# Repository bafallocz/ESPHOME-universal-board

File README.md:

# ESPHOME-universal-board

Modular, multi-purpose automation control boards designed around the **Seeed Studio XIAO** form-factor (ESP32-C3 / S3 / RP2040), tailored for **ESPHome**, **Home Assistant**, and standalone embedded automation projects.

The system consists of three hardware revisions/modules:
1. **Universal Board (Full Version)** – High-density I/O, mains-powered, precision analog/PWM expansion, gate-driven power MOSFETs, and relays.
2. **Universal Board (Light Version)** – Compact DC-powered board with direct logic-level SMD MOSFETs, relays, and inputs.
3. **Relay Expansion Board (Stackable)** – Dedicated 5-channel relay daughterboard controlled via the Full version's I2C PWM expander.

---

## Hardware Overview & Specifications

### 1. Board One: Full Version (Flagship)

Designed as a central automation node capable of direct 230 V mains operation, multi-channel high-current PWM control, mixed-signal ADC/DAC sensing, and galvanic isolation.

* **Core MCU:** Socket for Seeed Studio XIAO module (ESP32-C3, ESP32-S3, etc.).
* **Power Supply Options:**
  * **Mains AC Input:** Onboard **Hi-Link HLK-20M12** (20 W, 12 V / 1.66 A) isolated AC/DC power supply.
  * **Mains Protection:** 10D561K Metal Oxide Varistor (MOV) for surge and transient suppression.
  * **DC Input:** 2.1 mm DC Barrel Jack (`PJ-102AH`) for external 12 V DC supply.
  * **Step-Down:** Footprint for LM7805 LDO or pin-compatible high-efficiency DC-DC switching buck regulator (12 V to 5 V).
* **Power Outputs (4x High-Current PWM):**
  * **MOSFETs:** TO-220 footprint (tested with **IRL540N** / **IRFB4110PBF**).
  * **Gate Drivers:** Dual high-speed drivers (**TC4427** running at 12 V rail). Delivers up to 1.5 A peak gate drive current for fast switching transitions and minimal thermal loss during high-frequency PWM.
  * **Ratings:** Up to 60 V DC, 10 A burst / 5 A continuous per channel (dependent on PCB copper weight and heatsinking).
* **Analog & Precision I/O:**
  * **Analog Devices AD5593R** (12-bit, 8-channel configurable ADC / DAC / GPIO via I2C).
  * Onboard 2.5 V low-drift reference (`VREF`), filtered analog supplies, and dedicated 8-pin terminal/pin header.
* **Expanded PWM:**
  * **NXP PCA9685PW** (16-channel, 12-bit I2C PWM controller).
  * Channel `LED0` can be routed to high-current output/dimming, remaining channels (`EX_PWM1`–`EX_PWM15`) routed to stack header `JP1`.
* **Relays (2x Isolated):**
  * **Songle SRD-05VDC-SL-C** SPDT relays (rated 250 VAC / 10 A, 30 VDC / 10 A).
  * **Isolation & Drive:** Opto-isolated via **CPC1018N** 1-Form-A Solid State Relays (SSR) to isolate MCU logic from inductive switching spikes.
  * Flyback protection diodes on each coil.
* **Digital Inputs (2x Terminals):**
  * Dedicated screw terminals with 1k series current limiting.
  * **Nexperia PESD3V3L2BT** TVS/ESD diode array for surge/ESD protection on 3.3 V logic.
* **Expansion:** All unused XIAO GPIOs routed to standard 2.54 mm pin headers (`PHD1`, `PHD2`).

---

### 2. Board Two: Light Version

A low-profile, cost-optimized DC-powered board ideal for decentralized sub-nodes, LED strip dimming, and valve/motor switching.

* **Core MCU:** Seeed Studio XIAO module footprint.
* **Power Supply:**
  * DC Barrel Jack (`PJ-102AH`) feeding a dedicated pin-compatible DC-DC Step-Down module.
  * USB-C 5 V powering option with selectable `U_SEL` power routing jumper.
* **Power Outputs (3x SMD PWM):**
  * **MOSFETs:** **AO3400A** (N-channel, 30 V / 5.7 A).
  * Driven directly from MCU GPIOs.
  * Ideal for 12 V / 24 V LED strips (up to 3 A continuous per channel without forced cooling).
* **Relays (2x):**
  * 2x **SRD-05VDC-SL-C** driven via **CPC1018N** solid-state optical switches.
* **Digital Inputs (2x):**
  * Terminal block inputs with pull-ups/pull-downs for reed switches, dry contacts, or external buttons.
* **Expansion:** Unused pins broken out to side headers for I2C or SPI sensors.

---

### 3. Board Three: Expansion Board (Stackable)

An add-on hat designed to mount directly onto the **Full Version** via headers `PHD1`, `PHD2`, and `JP1`.

* **5x Additional Relays:** **SRD-05VDC-SL-C** (230 VAC / 10 A contact rating).
* **Control Bus:** Driven directly by the Full Board’s **PCA9685** PWM/GPIO expander (`EX_PWM1` through `EX_PWM5`).
* **Isolation:** Each relay coil is switched through an independent **CPC1018N** optical isolation relay.
* **Pass-through Routing:**
  * Leaves `EX_PWM6`–`EX_PWM15` available for additional servo or PWM peripherals.
  * Passes through AD5593R DAC/ADC lines and spare MCU GPIOs.

---

## Hardware Operating Limits & Safety Guidelines

> [!WARNING]
> **Mains Voltage Hazard:** The Full Version contains exposed 230 VAC tracks. Always install in an insulated DIN-rail or 3D-printed enclosure (**FR MATERIAL**). Maintain appropriate creepage and clearance distances between mains tracks and low-voltage logic.

* **Relay Contacts:** Rated for 10 A @ 250 VAC resistive load. For inductive loads (motors, pumps, contactors).
* **Full Board PWM Channels:** While the MOSFETs (IRFB4110 / IRL540N) have high silicon current ratings.
* **Light Board PWM Channels:** AO3400A is rated for 5.7 A peak; recommended continuous load per channel is **2.5 A to 3 A** without a copper heatsink pour.
* **Power Supply Headroom:** The HLK-20M12 provides up to 1.66 A at 12 V. When running multiple relays and external 12 V loads simultaneously, verify total DC power consumption remains under 20 W.

---

## AD5593R ESPHome Component

This repository includes a custom ESPHome component for the **Analog Devices AD5593R** (8-channel 12-bit configurable ADC / DAC / GPIO).

### How to Import into ESPHome

Add the `external_components` block to your YAML configuration:

#### Option A: Direct from GitHub
```yaml
external_components:
  - source: github://bafallocz/ESPHOME-universal-board
    components: [ ad5593r ]
```

#### Option B: Local Component (when compiling inside this repo)
```yaml
external_components:
  - source: components
    components: [ ad5593r ]
```

---

### AD5593R Configuration Guide

Any of the 8 pins (`0` to `7`) can be independently configured as an **ADC input**, **DAC output**, **Digital input (`binary_sensor`)**, or **Digital output (`switch`)**.

#### 1. Hub Definition
```yaml
ad5593r:
  - id: ad5593r_hub
    i2c_id: bus_a
    address: 0x10
    # reference_voltage: 2.5V  # Internal reference (default 2.5V)
    # gain_2x: true            # Default true -> Full range 0 to 5.0 V
```

#### 2. Analog Outputs (DAC) - Channels 0 to 7
Outputs range from `0.0` (0 V) to `1.0` (5.0 V):
```yaml
output:
  - platform: ad5593r
    ad5593r_id: ad5593r_hub
    channel: 0
    id: dac_out_0

  - platform: ad5593r
    ad5593r_id: ad5593r_hub
    channel: 1
    id: dac_out_1
```

Control DAC outputs using a Home Assistant template slider:
```yaml
number:
  - platform: template
    name: "DAC 0 Output"
    min_value: 0
    max_value: 1
    step: 0.01
    mode: slider
    set_action:
      - output.set_level:
          id: dac_out_0
          level: !lambda 'return x;'
```

#### 3. Analog Inputs (ADC) & Internal Temperature Sensor
Reports voltage values in **Volts (V)**:
```yaml
sensor:
  - platform: ad5593r
    ad5593r_id: ad5593r_hub
    channel: 2
    name: "AD5593R Analog Input 2"
    update_interval: 1s

  - platform: ad5593r
    ad5593r_id: ad5593r_hub
    channel: 3
    name: "AD5593R Analog Input 3"
    update_interval: 1s

  # Chip Internal Temperature Sensor (°C)
  - platform: ad5593r
    ad5593r_id: ad5593r_hub
    channel: temperature
    name: "AD5593R Internal Temperature"
    update_interval: 10s
```

#### 4. Digital Inputs (`binary_sensor`)
Reads logic state from pins (with optional 85 kΩ internal pull-down):
```yaml
binary_sensor:
  - platform: ad5593r
    ad5593r_id: ad5593r_hub
    channel: 4
    name: "AD5593R Digital Input 4"
    pulldown: true
```

#### 5. Digital Outputs (`switch`)
Controls digital output logic high/low on pins:
```yaml
switch:
  - platform: ad5593r
    ad5593r_id: ad5593r_hub
    channel: 5
    name: "AD5593R Digital Output 5"
```

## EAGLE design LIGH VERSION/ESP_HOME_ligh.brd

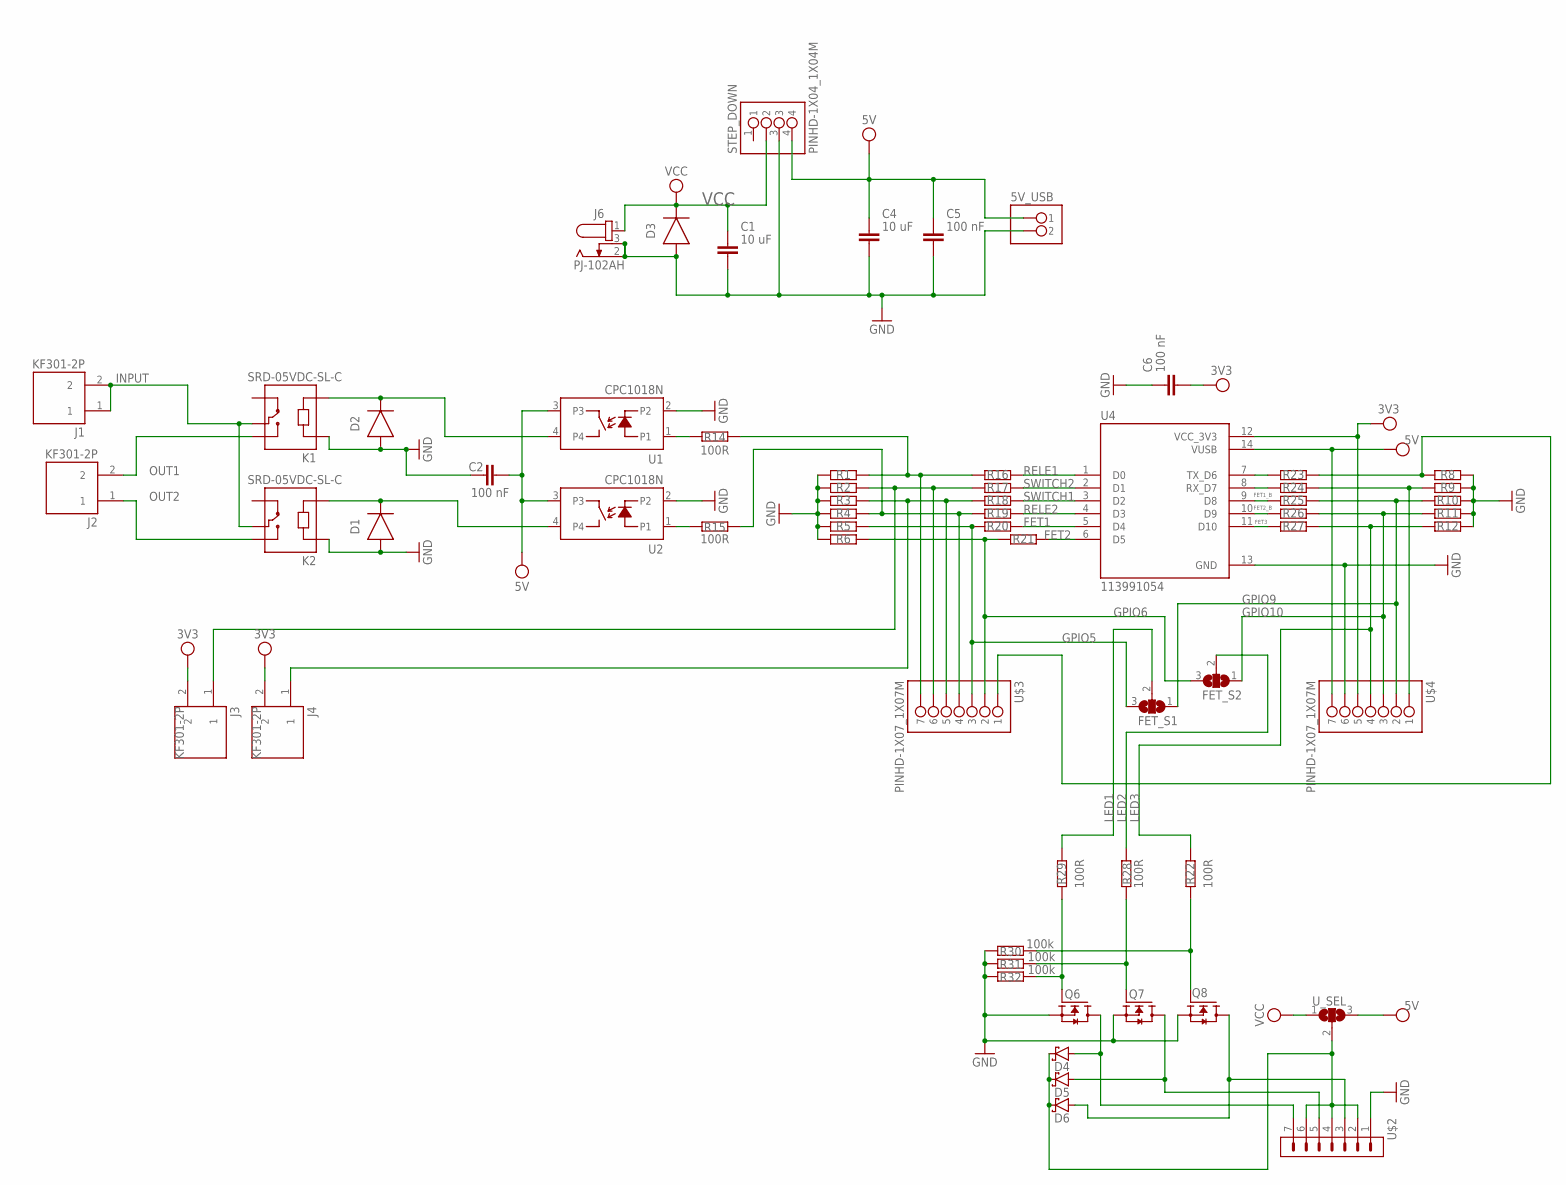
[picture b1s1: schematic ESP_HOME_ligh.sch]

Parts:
5V_USB: PINHD-1X02_1X02M; 1X02
C1, C4: 10 uF; CAPC2012X110
C2, C5, C6: 100 nF; CAPC2012X110
D1, D2, D3: DIODEDIODE-AXIAL; DIODE-AXIAL
D4, D5, D6: SCHOTTKY_MBR0520LT1GDO-219; SODFL3718X115
FET_S1, FET_S2: SJ2W; SJ_2
J1, J2, J3, J4: KF301-2P; HANDSON_KF301-2P
J6: PJ-102AH
K1, K2: SRD-05VDC-SL-C; RELAY_SRD-05VDC-SL-C
Q6, Q7, Q8: AO3400A; SOT95P280X125-3N
R1, R2, R3, R4, R5, R6, R8, R9, R10, R11, R12, R16, R17, R18, R19, R20, R21, R23, R24, R25, R26, R27: R_CHIP-1206(3216-METRIC); RESC3216X70
R14, R15, R22, R28, R29: 100R; RESC3216X70
R30, R31, R32: 100k; RESC3216X70
STEP_DOWN: PINHD-1X04_1X04M; 1X04
U1, U2: CPC1018N; CLARE_SO4
U4: 113991054; MODULE_113991054
U$2: PINHD-1X7; 1X07
U$3, U$4: PINHD-1X07_1X07M; 1X07
U_SEL: SJ2W; SJ_2

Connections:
3V3: C6.2, J3.2, J4.2, U4.12 (VCC_3V3), U$4.5
5V: 5V_USB.1, C2.2, C4.1, C5.1, STEP_DOWN.4, U1.3, U2.3, U4.14 (VUSB), U$4.7, U_SEL.3
FET1: R20.2, U4.5 (D4)
FET1_B: R25.1, U4.9 (D8)
FET2: R21.2, U4.6 (D5)
FET2_B: R26.1, U4.10 (D9)
FET3: R27.1, U4.11 (D10)
GND: 5V_USB.2, C1.2, C2.1, C4.2, C5.2, C6.1, D1.1 (A), D2.1 (A), D3.1 (A), J6.2, J6.3, K1.A1, K2.A1, Q6.2 (S), Q7.2 (S), Q8.2 (S), R1.1, R2.1, R3.1, R4.1, R5.1, R6.1, R8.2, R9.2, R10.2, R11.2, R12.2, R30.2, R31.2, R32.2, STEP_DOWN.3, U1.2, U2.2, U4.13 (GND), U$2.1, U$4.6
GPIO5: FET_S1.3, R5.2, R20.1, U$3.3
GPIO6: FET_S2.3, R6.2, R21.1, U$3.2
GPIO9: FET_S1.1, R10.1, R25.2, U$4.2
GPIO10: FET_S2.1, R11.1, R26.2, U$4.3
INPUT: J1.1, J1.2, K1.COM, K2.COM
LED1: FET_S1.2, R29.2
LED2: FET_S2.2, R28.1
LED3: R12.1, R22.2, R27.2, U$4.4
unnamed: R14.2, U1.1
unnamed: D4.2 (A), Q6.3 (D), U$2.7
unnamed: R23.1, U4.7 (TX_D6)
unnamed: R24.1, U4.8 (RX_D7)
unnamed: Q6.1 (G), R29.1, R32.1
unnamed: Q7.1 (G), R28.2, R31.1
unnamed: Q8.1 (G), R22.1, R30.1
unnamed: R15.2, U2.1
unnamed: D1.2 (C), K2.A2, U2.4
unnamed: D2.2 (C), K1.A2, U1.4
unnamed: R9.1, R24.2, U$4.1
unnamed: R8.1, R23.2, U$3.1
unnamed: R4.2, R15.1, R19.1, U$3.4
unnamed: D4.1 (C), D5.1 (C), D6.1 (C), U$2.2, U$2.4, U$2.6, U_SEL.2
unnamed: D5.2 (A), Q7.3 (D), U$2.5
unnamed: D6.2 (A), Q8.3 (D), U$2.3
unnamed: R1.2, R14.1, R16.1, U$3.7
OUT1: J2.2, K1.NO
OUT2: J2.1, K2.NO
RELE1: R16.2, U4.1 (D0)
RELE2: R19.2, U4.4 (D3)
SW1: J3.1, R2.2, R17.1, U$3.6
SW2: J4.1, R3.2, R18.1, U$3.5
SWITCH1: R18.2, U4.3 (D2)
SWITCH2: R17.2, U4.2 (D1)
VCC: C1.1, D3.2 (C), J6.1, STEP_DOWN.2, U_SEL.1

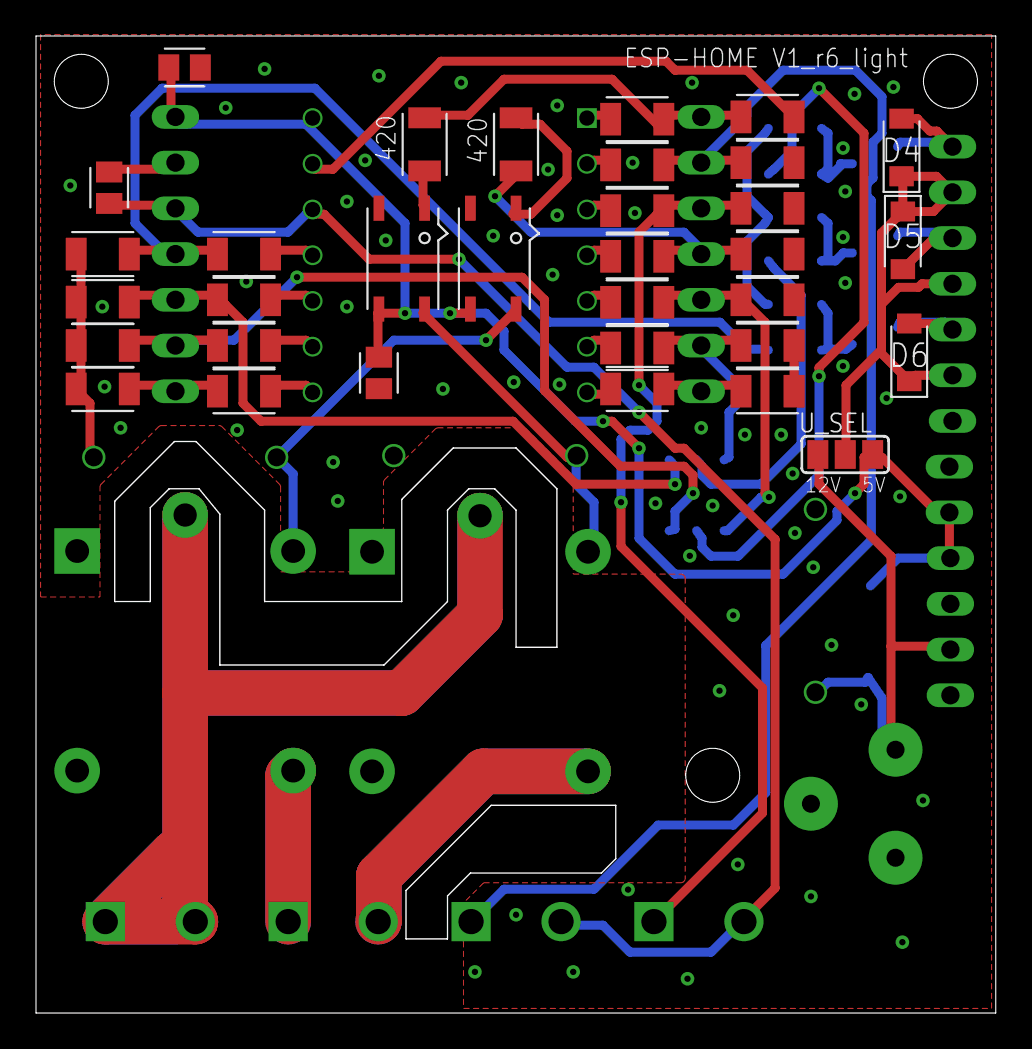
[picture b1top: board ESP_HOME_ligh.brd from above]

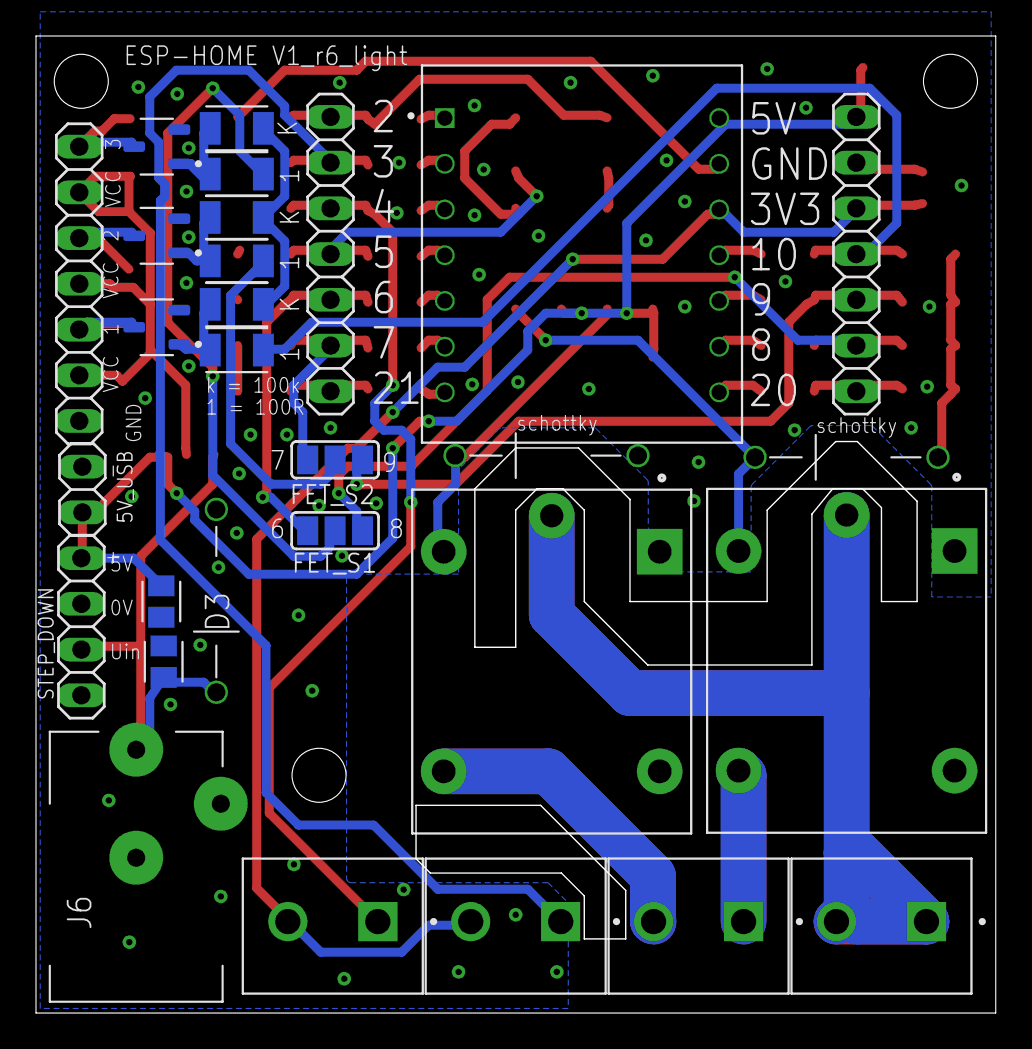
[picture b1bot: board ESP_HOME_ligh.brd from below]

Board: 2 copper layers, 53.3 x 54.3 mm, 62 parts (29 on the bottom side), 42 nets.

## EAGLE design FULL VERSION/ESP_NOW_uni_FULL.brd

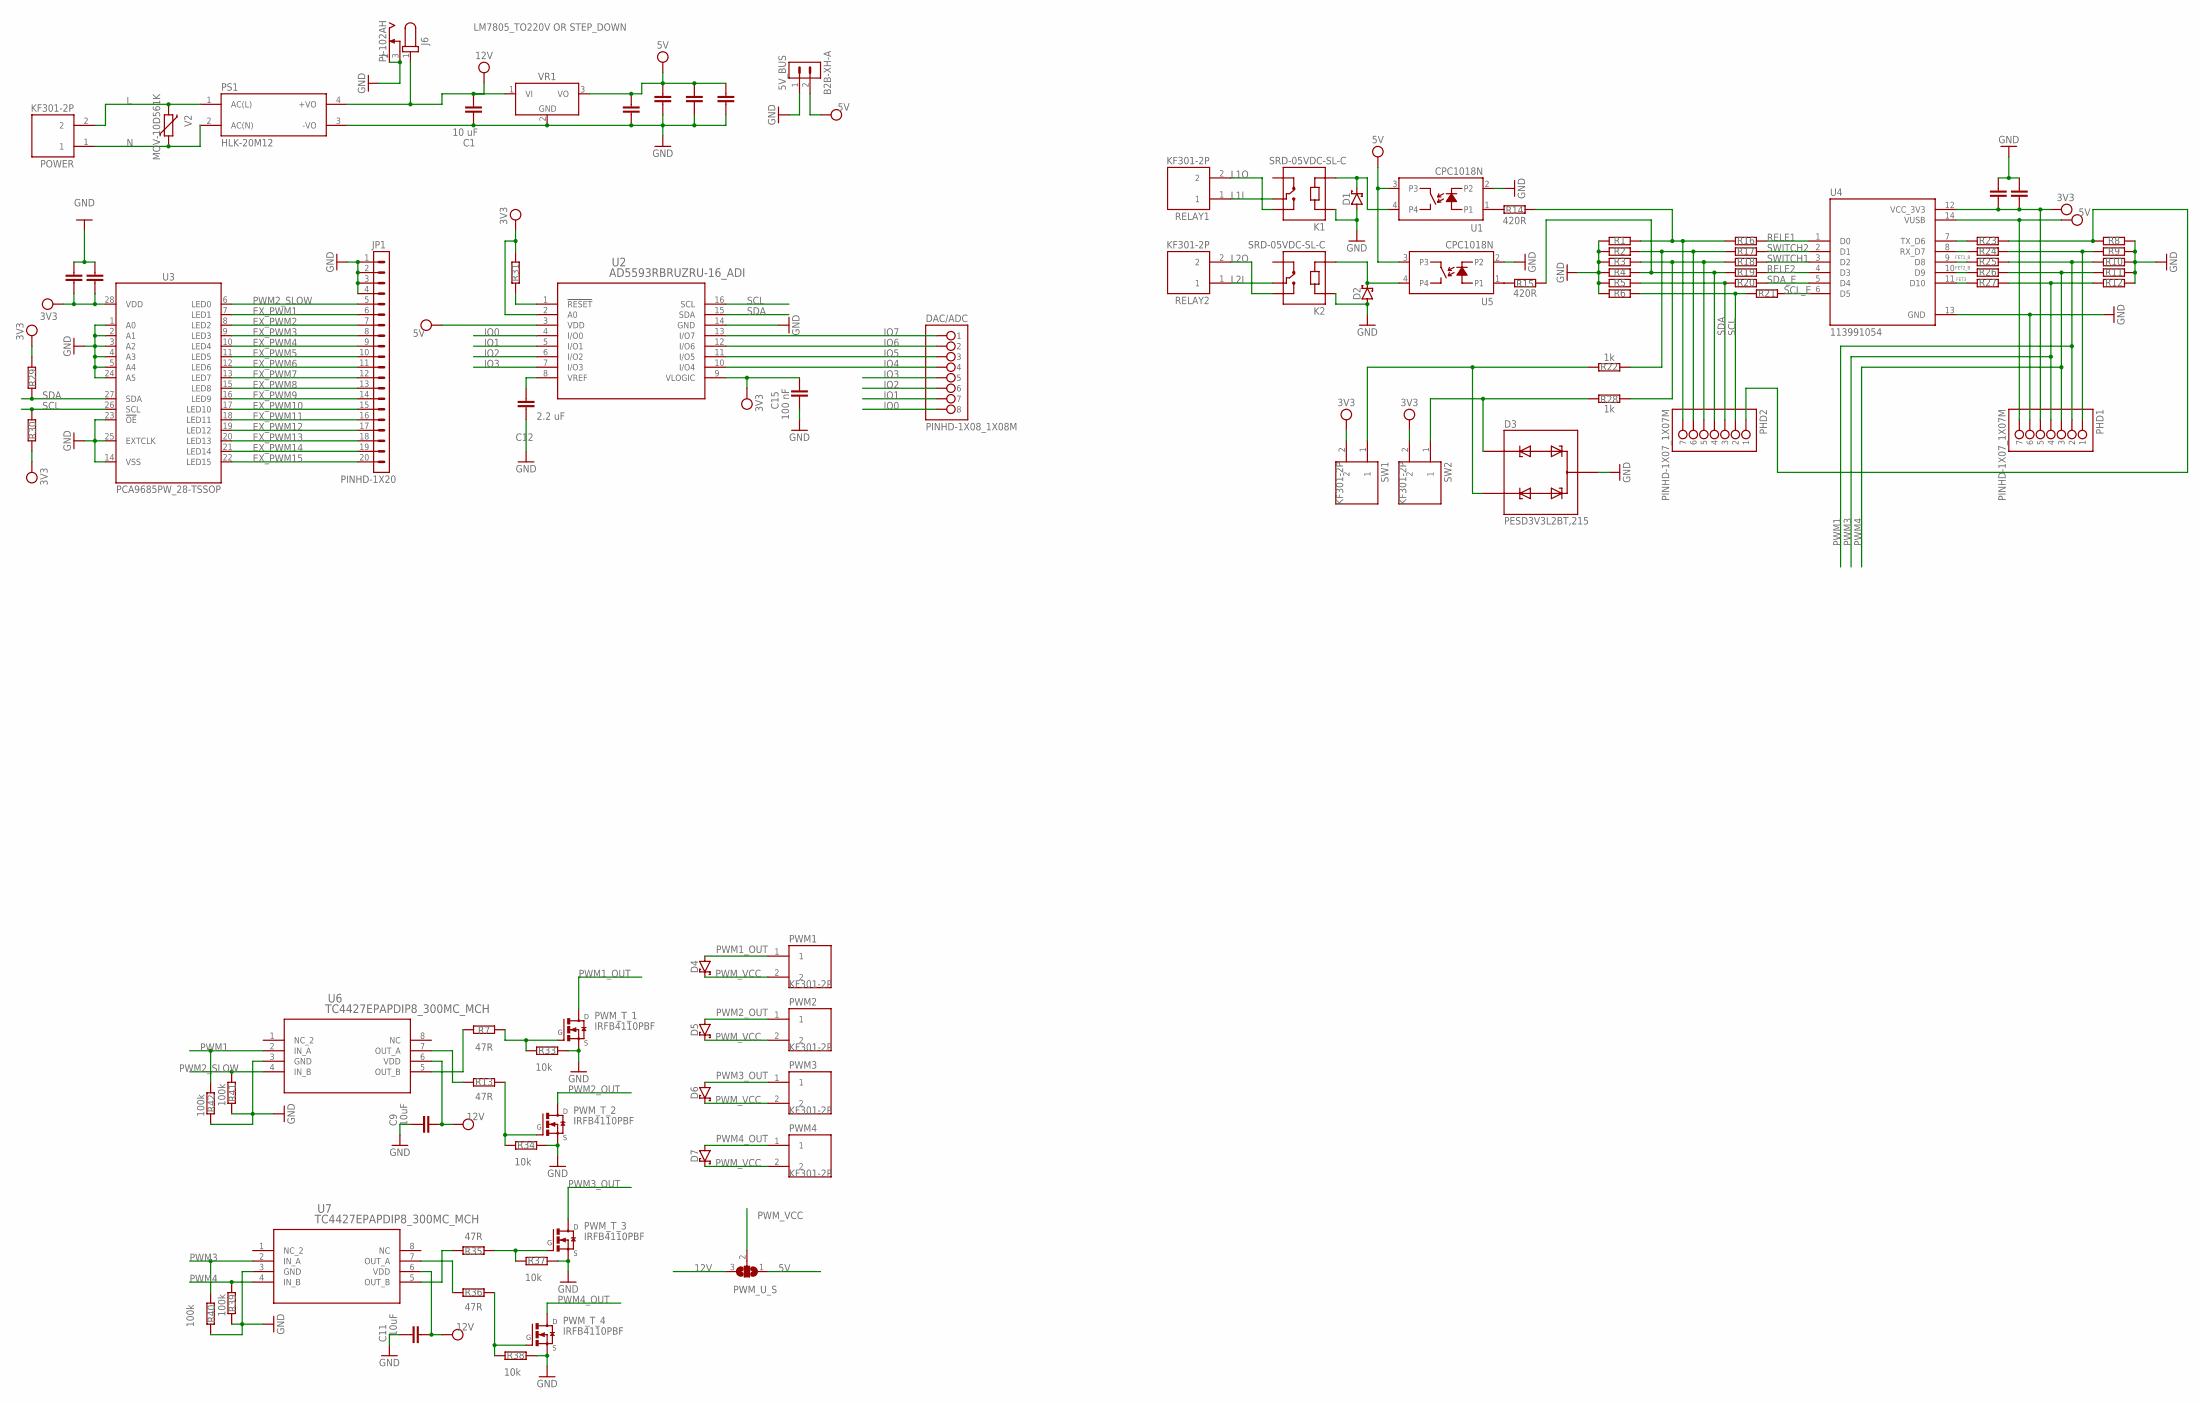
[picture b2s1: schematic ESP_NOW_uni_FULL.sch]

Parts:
5V_BUS: B2B-XH-A
C1: 10 uF; CAPC2012X110
C2: 0.1uF; CAPC2012X110
C3, C4, C5, C6, C7, C8, C9, C10, C11: 10uF; CAPC2012X110
C12: 2.2 uF; CAPC2012X110
C15: 100 nF; CAPC2012X110
D1, D2, D4, D5, D6, D7: SCHOTTKY_MBR0520LT1GDO-219; SODFL3718X115
D3: PESD3V3L2BT,215; SOT95P230X110-3N
DAC/ADC: PINHD-1X08_1X08M; 1X08
J6: PJ-102AH
JP1: PINHD-1X20; 1X20
K1, K2: SRD-05VDC-SL-C; RELAY_SRD-05VDC-SL-C
PHD1, PHD2: PINHD-1X07_1X07M; 1X07
POWER: KF301-2P; HANDSON_KF301-2P
PS1: HLK-20M12; CONV_HLK-20M12
PWM1, PWM2, PWM3, PWM4: KF301-2P; HANDSON_KF301-2P
PWM_T_1, PWM_T_2, PWM_T_3, PWM_T_4: IRFB4110PBF; TO220V
PWM_U_S: SJ2W; SJ_2
R1, R2, R3, R4, R5, R6, R8, R9, R10, R11, R12, R16, R17, R18, R19, R20, R21, R23, R24, R25, R26, R27, R29, R30, R31: R_CHIP-0603(1608-METRIC); RESC1608X60
R7, R13, R35, R36: 47R; RESC1608X60
R14, R15: 420R; RESC1608X60
R22, R28: 1k; RESC1608X60
R33, R34, R37, R38: 10k; RESC1608X60
R39, R40, R41, R42: 100k; RESC1608X60
RELAY1, RELAY2: KF301-2P; HANDSON_KF301-2P
SW1, SW2: KF301-2P; HANDSON_KF301-2P
U1, U5: CPC1018N; CLARE_SO4
U2: AD5593RBRUZRU-16_ADI; RU-16_ADI
U3: PCA9685PW_28-TSSOP; SOP65P640X110-28
U4: 113991054; MODULE_113991054
U6, U7: TC4427EPAPDIP8_300MC_MCH; PDIP8_300MC_MCH
V2: MOV-10D561K; MOV-10D561
VR1: LM7805_TO220V OR STEP_DOWN; TO220V

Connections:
3V3: C6.2, C7.2, C8.2, C10.2, C15.1, PHD1.5, R29.1, R30.2, R31.2, SW1.2, SW2.2, U2.2 (A0), U2.9 (VLOGIC), U3.28 (VDD), U4.12 (VCC_3V3)
5V: 5V_BUS.2, C2.1, C3.1, C4.1, C5.1, PHD1.7, PWM_U_S.1, U1.3, U2.3 (VDD), U4.14 (VUSB), U5.3, VR1.3 (VO)
12V: C1.1, C9.1, C11.1, J6.1, PS1.4 (+VO), PWM_U_S.3, U6.6 (VDD), U7.6 (VDD), VR1.1 (VI)
EX_PWM1: JP1.6, U3.7 (LED1)
EX_PWM2: JP1.7, U3.8 (LED2)
EX_PWM3: JP1.8, U3.9 (LED3)
EX_PWM4: JP1.9, U3.10 (LED4)
EX_PWM5: JP1.10, U3.11 (LED5)
EX_PWM6: JP1.11, U3.12 (LED6)
EX_PWM7: JP1.12, U3.13 (LED7)
EX_PWM8: JP1.13, U3.15 (LED8)
EX_PWM9: JP1.14, U3.16 (LED9)
EX_PWM10: JP1.15, U3.17 (LED10)
EX_PWM11: JP1.16, U3.18 (LED11)
EX_PWM12: JP1.17, U3.19 (LED12)
EX_PWM13: JP1.18, U3.20 (LED13)
EX_PWM14: JP1.19, U3.21 (LED14)
EX_PWM15: JP1.20, U3.22 (LED15)
FET1_B: R25.1, U4.9 (D8)
FET2_B: R26.1, U4.10 (D9)
FET3: R27.1, U4.11 (D10)
GND: 5V_BUS.1, C1.2, C2.2, C3.2, C4.2, C5.2, C6.1, C7.1, C8.1, C9.2, C10.1, C11.2, C12.2, C15.2, D1.2 (A), D2.2 (A), D3.3 (CC), J6.2, J6.3, JP1.1, JP1.2, JP1.3, JP1.4, K1.A1, K2.A1, PHD1.6, PS1.3 (-VO), PWM_T_1.3 (S), PWM_T_2.3 (S), PWM_T_3.3 (S), PWM_T_4.3 (S), R1.1, R2.1, R3.1, R4.1, R5.1, R6.1, R8.2, R9.2, R10.2, R11.2, R12.2, R33.2, R34.2, R37.2, R38.2, R39.2, R40.2, R41.2, R42.2, U1.2, U2.14 (GND), U3.1 (A0), U3.2 (A1), U3.3 (A2), U3.4 (A3), U3.5 (A4), U3.14 (VSS), U3.23 (!OE), U3.24 (A5), U3.25 (EXTCLK), U4.13 (GND), U5.2, U6.3 (GND), U7.3 (GND), VR1.2 (GND)
IO0: DAC/ADC.8, U2.4 (I/O0)
IO1: DAC/ADC.7, U2.5 (I/O1)
IO2: DAC/ADC.6, U2.6 (I/O2)
IO3: DAC/ADC.5, U2.7 (I/O3)
IO4: DAC/ADC.4, U2.10 (I/O4)
IO5: DAC/ADC.3, U2.11 (I/O5)
IO6: DAC/ADC.2, U2.12 (I/O6)
IO7: DAC/ADC.1, U2.13 (I/O7)
L: POWER.2, PS1.1 (AC(L)), V2.2
L1I: K1.COM, RELAY1.1
L1O: K1.NO, RELAY1.2
L2I: K2.COM, RELAY2.1
L2O: K2.NO, RELAY2.2
N: POWER.1, PS1.2 (AC(N)), V2.1
unnamed: PWM_T_1.1 (G), R7.1, R33.1
unnamed: D3.2 (K2), R22.1, SW1.1
unnamed: R23.1, U4.7 (TX_D6)
unnamed: R24.1, U4.8 (RX_D7)
unnamed: D3.1 (K1), R28.2, SW2.1
unnamed: C12.1, U2.8 (VREF)
unnamed: D2.1 (C), K2.A2, U5.4
unnamed: D1.1 (C), K1.A2, U1.4
unnamed: R31.1, U2.1 (!RESET)
unnamed: PWM_T_2.1 (G), R13.2, R34.1
unnamed: PWM_T_3.1 (G), R35.1, R37.1
unnamed: PHD1.1, R9.1, R24.2
unnamed: PHD2.1, R8.1, R23.2
unnamed: PWM_T_4.1 (G), R36.2, R38.1
unnamed: PHD2.4, R4.2, R15.1, R19.1
unnamed: R7.2, U6.5 (OUT_B)
unnamed: R14.2, U1.1
unnamed: R15.2, U5.1
unnamed: R13.1, U6.7 (OUT_A)
unnamed: R36.1, U7.7 (OUT_A)
unnamed: R35.2, U7.5 (OUT_B)
unnamed: PHD2.7, R1.2, R14.1, R16.1
PWM1: PHD1.2, R10.1, R25.2, R42.1, U6.2 (IN_A)
PWM1_OUT: D4.2 (A), PWM1.1, PWM_T_1.2 (D)
PWM2_OUT: D5.2 (A), PWM2.1, PWM_T_2.2 (D)
PWM2_SLOW: JP1.5, R41.1, U3.6 (LED0), U6.4 (IN_B)
PWM3: PHD1.4, R12.1, R27.2, R40.1, U7.2 (IN_A)
PWM3_OUT: D6.2 (A), PWM3.1, PWM_T_3.2 (D)
PWM4: PHD1.3, R11.1, R26.2, R39.1, U7.4 (IN_B)
PWM4_OUT: D7.2 (A), PWM4.1, PWM_T_4.2 (D)
PWM_VCC: D4.1 (C), D5.1 (C), D6.1 (C), D7.1 (C), PWM1.2, PWM2.2, PWM3.2, PWM4.2, PWM_U_S.2
RELE1: R16.2, U4.1 (D0)
RELE2: R19.2, U4.4 (D3)
SCL: PHD2.2, R6.2, R21.1, R30.1, U2.16 (SCL), U3.26 (SCL)
SCL_E: R21.2, U4.6 (D5)
SDA: PHD2.3, R5.2, R20.1, R29.2, U2.15 (SDA), U3.27 (SDA)
SDA_E: R20.2, U4.5 (D4)
SW1: PHD2.6, R2.2, R17.1, R22.2
SW2: PHD2.5, R3.2, R18.1, R28.1
SWITCH1: R18.2, U4.3 (D2)
SWITCH2: R17.2, U4.2 (D1)

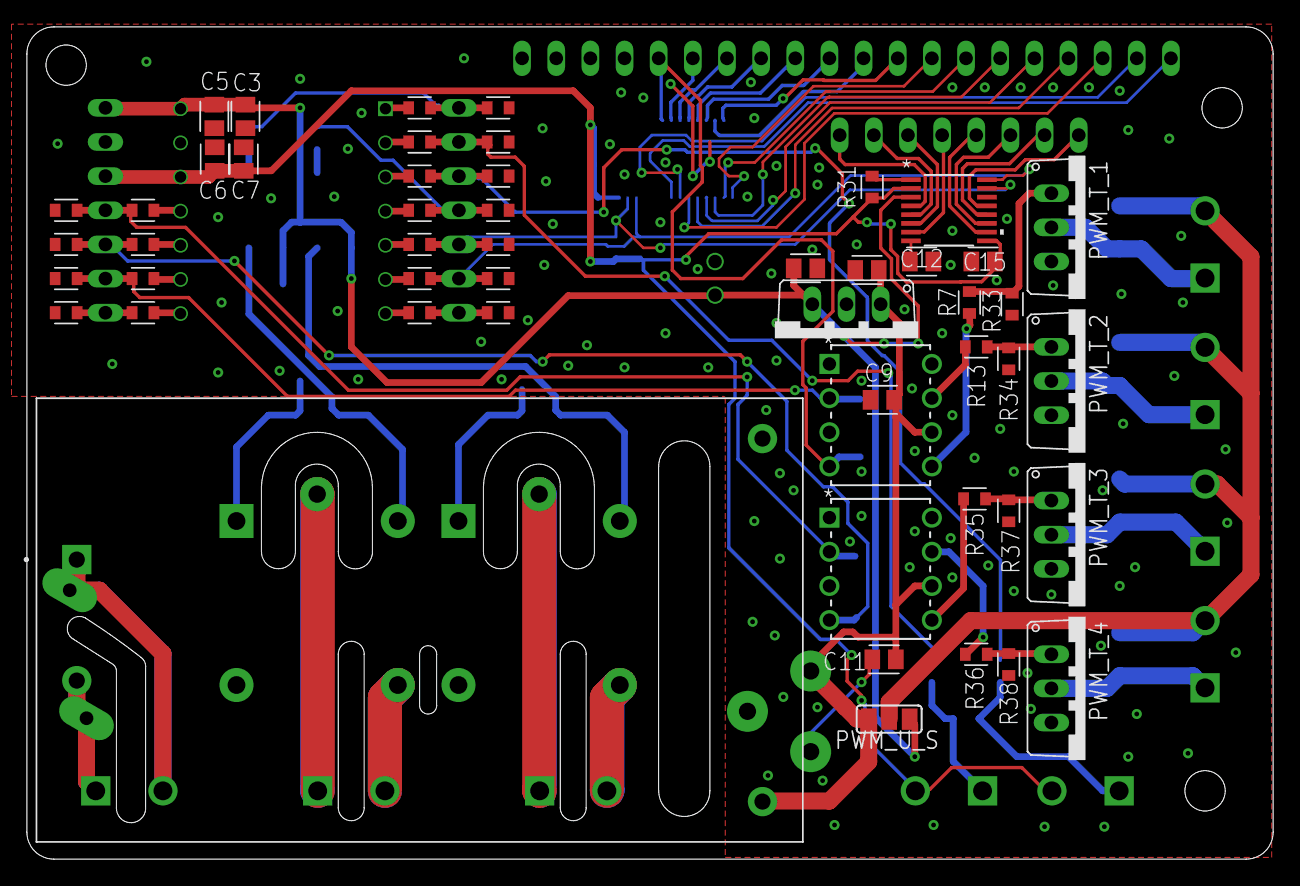
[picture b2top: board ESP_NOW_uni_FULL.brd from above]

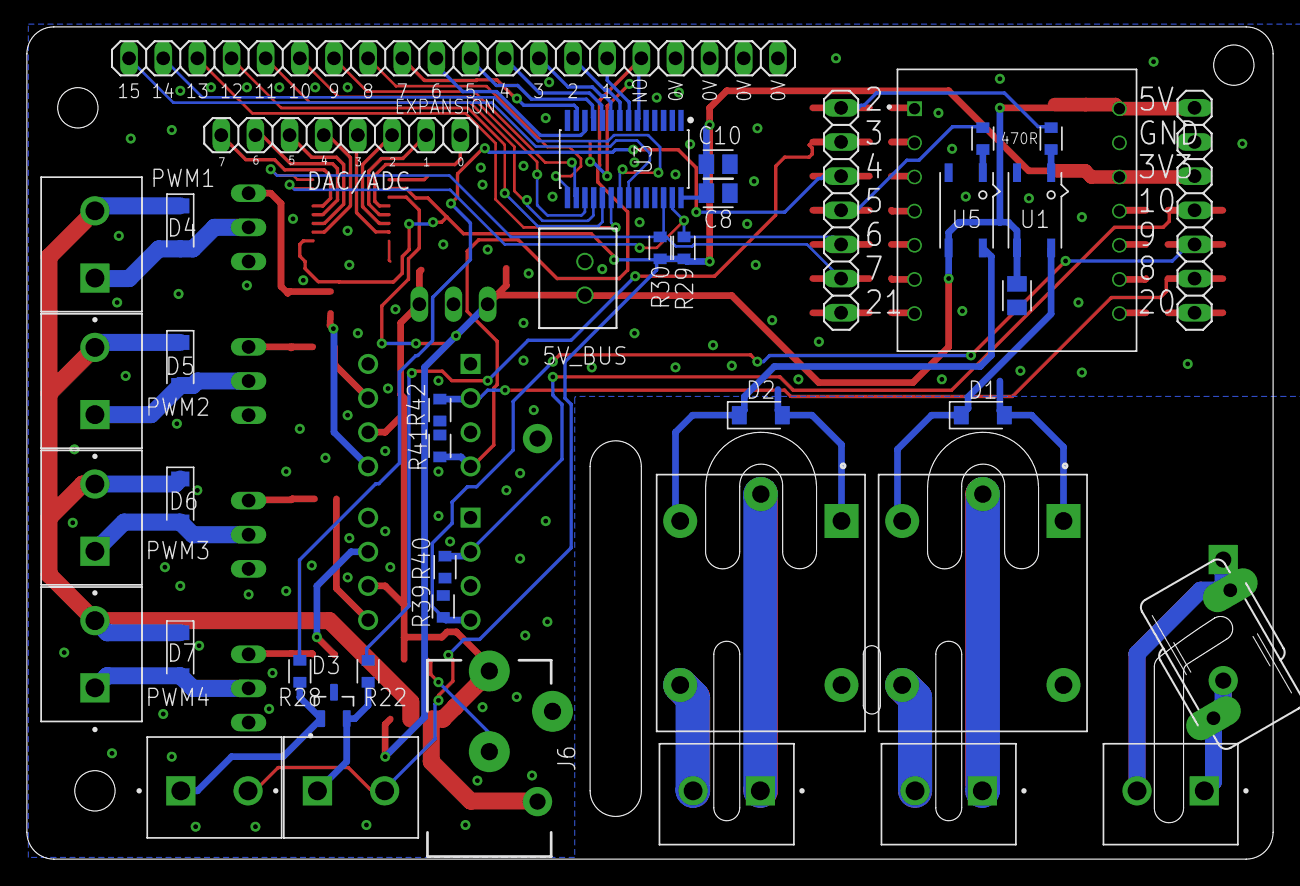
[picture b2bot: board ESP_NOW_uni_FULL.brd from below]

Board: 2 copper layers, 92.7 x 61.9 mm, 93 parts (42 on the bottom side), 77 nets.

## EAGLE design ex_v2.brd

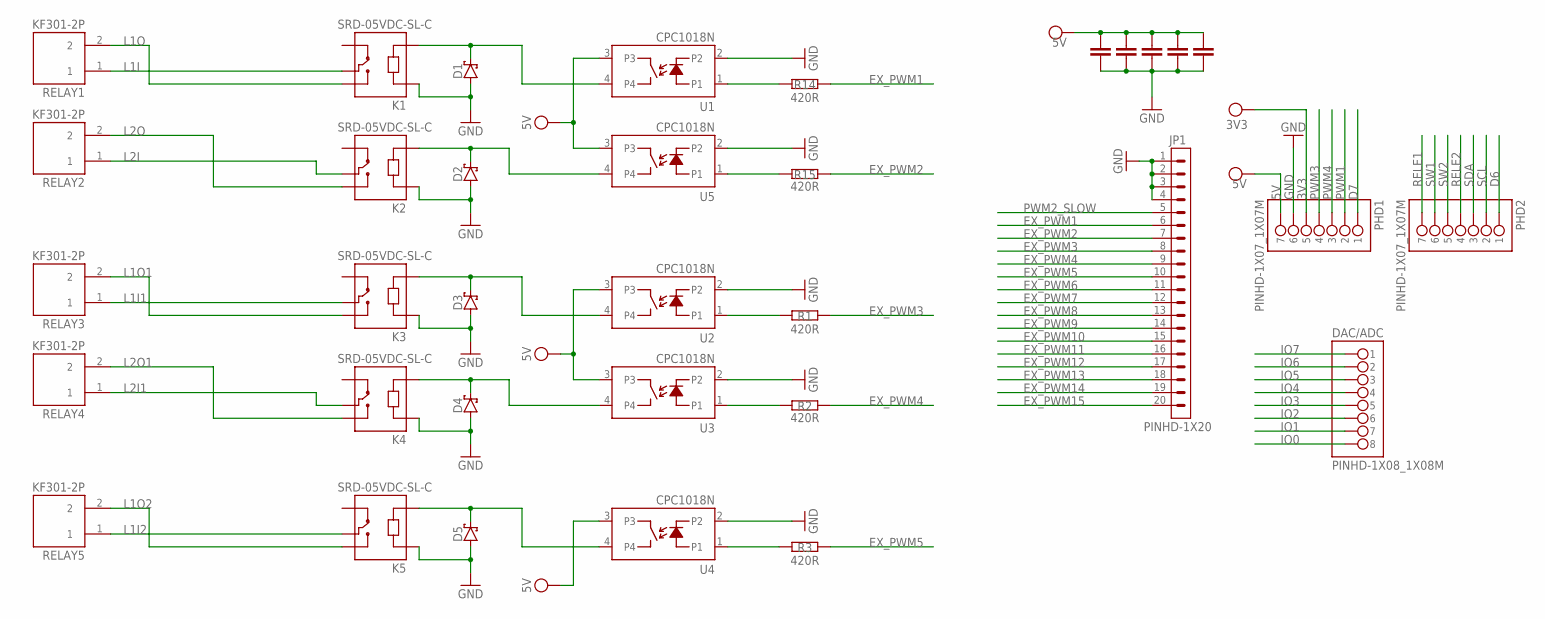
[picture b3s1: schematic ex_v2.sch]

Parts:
C1, C2, C3, C6, C8: 10uF; CAPC2012X110
D1, D2, D3, D4, D5: SCHOTTKY_MBR0520LT1GDO-219; SODFL3718X115
DAC/ADC: PINHD-1X08_1X08M; 1X08
JP1: PINHD-1X20; 1X20
K1, K2, K3, K4, K5: SRD-05VDC-SL-C; RELAY_SRD-05VDC-SL-C
PHD1, PHD2: PINHD-1X07_1X07M; 1X07
R1, R2, R3, R14, R15: 420R; RESC1608X60
RELAY1, RELAY2, RELAY3, RELAY4, RELAY5: KF301-2P; HANDSON_KF301-2P
U1, U2, U3, U4, U5: CPC1018N; CLARE_SO4

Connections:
3V3: PHD1.5
5V: C1.1, C2.1, C3.1, C6.1, C8.1, PHD1.7, U1.3, U2.3, U3.3, U4.3, U5.3
D6: PHD2.1
D7: PHD1.1
EX_PWM1: JP1.6, R14.1
EX_PWM2: JP1.7, R15.1
EX_PWM3: JP1.8, R1.1
EX_PWM4: JP1.9, R2.1
EX_PWM5: JP1.10, R3.1
EX_PWM6: JP1.11
EX_PWM7: JP1.12
EX_PWM8: JP1.13
EX_PWM9: JP1.14
EX_PWM10: JP1.15
EX_PWM11: JP1.16
EX_PWM12: JP1.17
EX_PWM13: JP1.18
EX_PWM14: JP1.19
EX_PWM15: JP1.20
GND: C1.2, C2.2, C3.2, C6.2, C8.2, D1.2 (A), D2.2 (A), D3.2 (A), D4.2 (A), D5.2 (A), JP1.1, JP1.2, JP1.3, JP1.4, K1.A1, K2.A1, K3.A1, K4.A1, K5.A1, PHD1.6, U1.2, U2.2, U3.2, U4.2, U5.2
IO0: DAC/ADC.8
IO1: DAC/ADC.7
IO2: DAC/ADC.6
IO3: DAC/ADC.5
IO4: DAC/ADC.4
IO5: DAC/ADC.3
IO6: DAC/ADC.2
IO7: DAC/ADC.1
L1I: K1.COM, RELAY1.1
L1I1: K3.COM, RELAY3.1
L1I2: K5.COM, RELAY5.1
L1O: K1.NO, RELAY1.2
L1O1: K3.NO, RELAY3.2
L1O2: K5.NO, RELAY5.2
L2I: K2.COM, RELAY2.1
L2I1: K4.COM, RELAY4.1
L2O: K2.NO, RELAY2.2
L2O1: K4.NO, RELAY4.2
unnamed: R1.2, U2.1
unnamed: R2.2, U3.1
unnamed: D4.1 (C), K4.A2, U3.4
unnamed: D3.1 (C), K3.A2, U2.4
unnamed: D2.1 (C), K2.A2, U5.4
unnamed: D1.1 (C), K1.A2, U1.4
unnamed: R3.2, U4.1
unnamed: D5.1 (C), K5.A2, U4.4
unnamed: R14.2, U1.1
unnamed: R15.2, U5.1
PWM1: PHD1.2
PWM2_SLOW: JP1.5
PWM3: PHD1.4
PWM4: PHD1.3
RELE1: PHD2.7
RELE2: PHD2.4
SCL: PHD2.2
SDA: PHD2.3
SW1: PHD2.6
SW2: PHD2.5

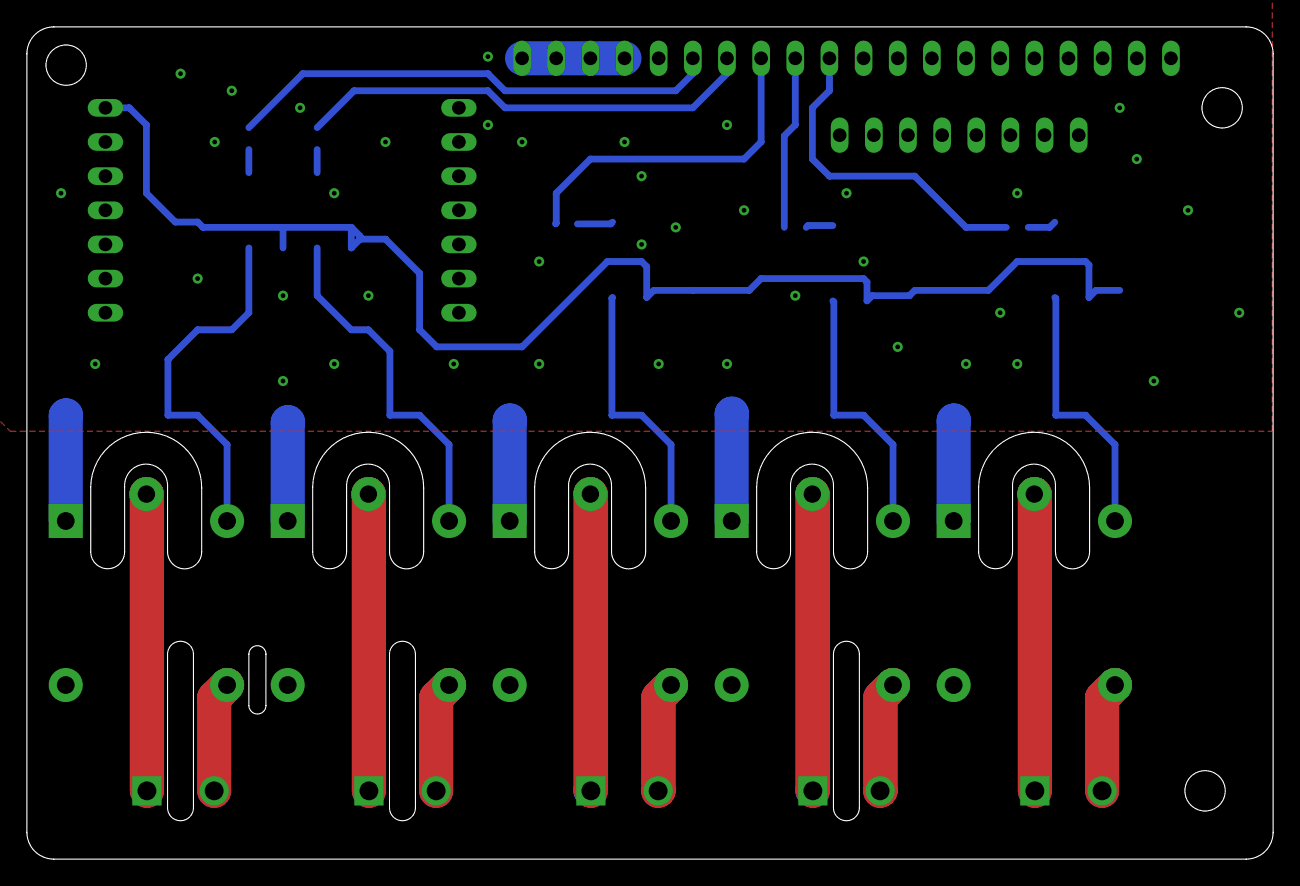
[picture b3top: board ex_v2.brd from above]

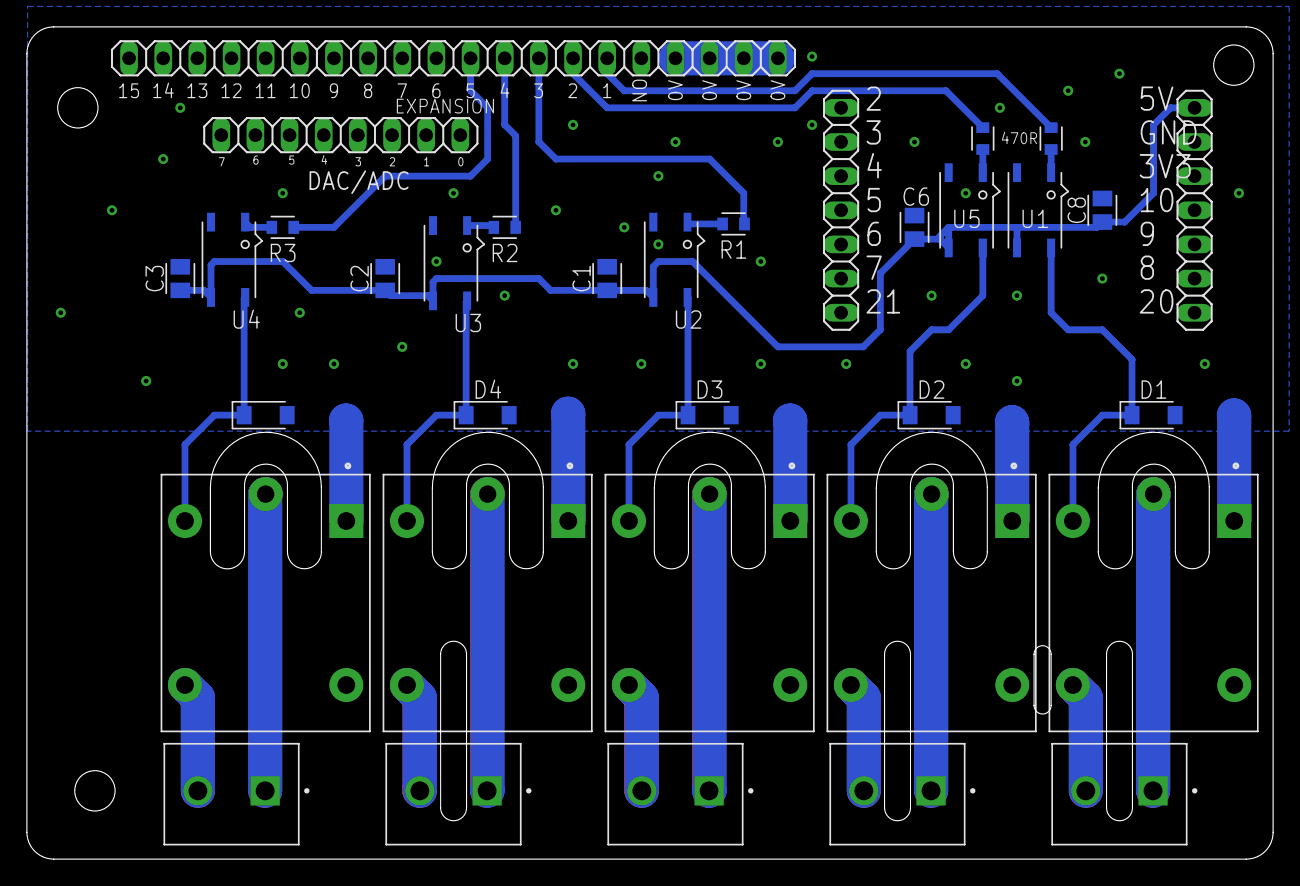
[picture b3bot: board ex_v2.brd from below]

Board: 2 copper layers, 92.7 x 61.9 mm, 34 parts (34 on the bottom side), 27 nets.

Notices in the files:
parts and their libraries:
COPYRIGHT: Copyright (C) 2026 Ultra Librarian. All rights reserved.
